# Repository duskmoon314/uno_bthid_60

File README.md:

# uno_bthid_60

Trying to diy a uno based, bluetooth HID 60 keyboard

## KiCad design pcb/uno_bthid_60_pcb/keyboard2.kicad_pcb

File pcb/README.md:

# README: uno_bthid_60_pcb

KiCAD project

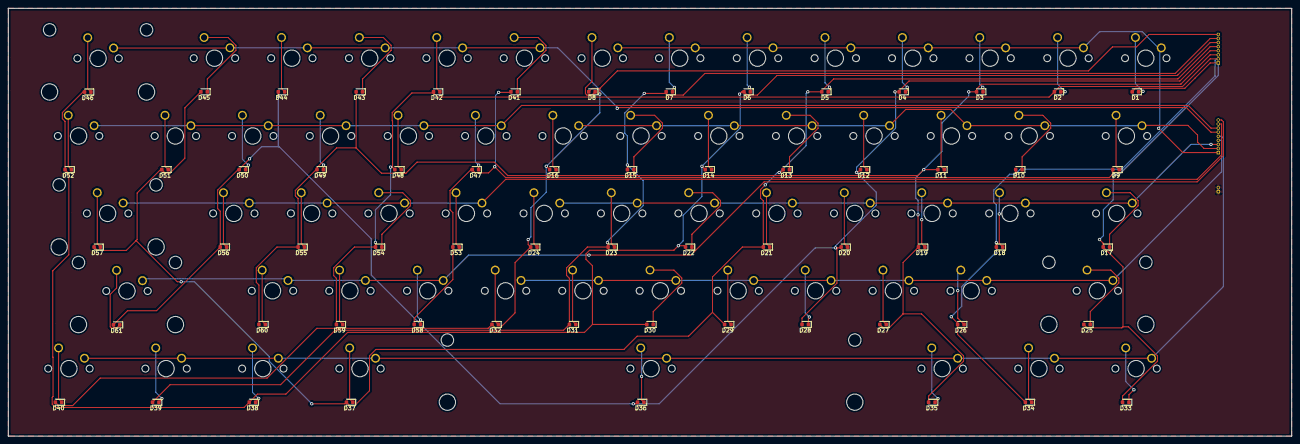
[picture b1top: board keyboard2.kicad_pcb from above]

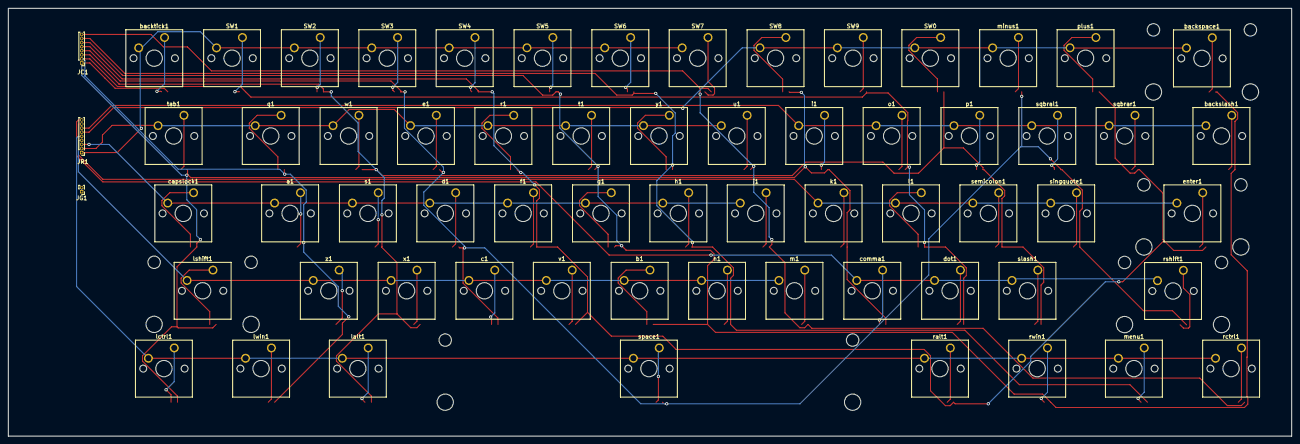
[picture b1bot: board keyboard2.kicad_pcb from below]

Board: 2 copper layers, 315.0 x 105.0 mm, 125 parts (64 on the bottom side), 79 nets.

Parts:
D1, D2, D3, D4, D5, D6, D7, D8, D9, D10, D11, D12, D13, D14, D15, D16, D17, D18, D19, D20, D21, D22, D23, D24, D25, D26, D27, D28, D29, D30, D31, D32, D33, D34, D35, D36, D37, D38, D39, D40, D41, D42, D43, D44, D45, D46, D47, D48, D49, D50, D51, D52, D53, D54, D55, D56, D57, D58, D59, D60, D61: DIODE; D_0603_1608Metric
JC1: Conn_01x08; PinHeader_1x08_P1.00mm_Vertical
JG1: Conn_01x02; PinHeader_1x02_P1.00mm_Vertical
JR1: Conn_01x09; PinHeader_1x09_P1.00mm_Vertical
SW0, SW1, SW2, SW3, SW4, SW5, SW6, SW7, SW8, SW9: SW_Push; SW_Cherry_MX_1.00u_PCB
a1: SW_Push; SW_Cherry_MX_1.00u_PCB
b1: SW_Push; SW_Cherry_MX_1.00u_PCB
backslash1: SW_Push; SW_Cherry_MX_1.50u_PCB
backspace1: SW_Push; SW_Cherry_MX_2.00u_PCB
backtick1: SW_Push; SW_Cherry_MX_1.00u_PCB
c1: SW_Push; SW_Cherry_MX_1.00u_PCB
capslock1: SW_Push; SW_Cherry_MX_1.75u_PCB
comma1: SW_Push; SW_Cherry_MX_1.00u_PCB
d1: SW_Push; SW_Cherry_MX_1.00u_PCB
dot1: SW_Push; SW_Cherry_MX_1.00u_PCB
e1: SW_Push; SW_Cherry_MX_1.00u_PCB
enter1: SW_Push; SW_Cherry_MX_2.25u_PCB
f1: SW_Push; SW_Cherry_MX_1.00u_PCB
g1: SW_Push; SW_Cherry_MX_1.00u_PCB
h1: SW_Push; SW_Cherry_MX_1.00u_PCB
i1: SW_Push; SW_Cherry_MX_1.00u_PCB
j1: SW_Push; SW_Cherry_MX_1.00u_PCB
k1: SW_Push; SW_Cherry_MX_1.00u_PCB
l1: SW_Push; SW_Cherry_MX_1.00u_PCB
lalt1: SW_Push; SW_Cherry_MX_1.25u_PCB
lctrl1: SW_Push; SW_Cherry_MX_1.25u_PCB
lshift1: SW_Push; SW_Cherry_MX_2.25u_PCB
lwin1: SW_Push; SW_Cherry_MX_1.25u_PCB
m1: SW_Push; SW_Cherry_MX_1.00u_PCB
menu1: SW_Push; SW_Cherry_MX_1.25u_PCB
minus1: SW_Push; SW_Cherry_MX_1.00u_PCB
n1: SW_Push; SW_Cherry_MX_1.00u_PCB
o1: SW_Push; SW_Cherry_MX_1.00u_PCB
p1: SW_Push; SW_Cherry_MX_1.00u_PCB
plus1: SW_Push; SW_Cherry_MX_1.00u_PCB
q1: SW_Push; SW_Cherry_MX_1.00u_PCB
r1: SW_Push; SW_Cherry_MX_1.00u_PCB
ralt1: SW_Push; SW_Cherry_MX_1.25u_PCB
rctrl1: SW_Push; SW_Cherry_MX_1.25u_PCB
rshift1: SW_Push; SW_Cherry_MX_2.75u_PCB
rwin1: SW_Push; SW_Cherry_MX_1.25u_PCB
s1: SW_Push; SW_Cherry_MX_1.00u_PCB
semicolon1: SW_Push; SW_Cherry_MX_1.00u_PCB
singquote1: SW_Push; SW_Cherry_MX_1.00u_PCB
slash1: SW_Push; SW_Cherry_MX_1.00u_PCB
space1: SW_Push; SW_Cherry_MX_6.25u_PCB
sqbral1: SW_Push; SW_Cherry_MX_1.00u_PCB
sqbrar1: SW_Push; SW_Cherry_MX_1.00u_PCB
t1: SW_Push; SW_Cherry_MX_1.00u_PCB
tab1: SW_Push; SW_Cherry_MX_1.50u_PCB
u1: SW_Push; SW_Cherry_MX_1.00u_PCB
v1: SW_Push; SW_Cherry_MX_1.00u_PCB
w1: SW_Push; SW_Cherry_MX_1.00u_PCB
x1: SW_Push; SW_Cherry_MX_1.00u_PCB
y1: SW_Push; SW_Cherry_MX_1.00u_PCB
z1: SW_Push; SW_Cherry_MX_1.00u_PCB

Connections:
/C1: D1.2, D9.2, D17.2, D25.2, D33.2, D41.2, D47.2, D53.2, D58.2, JC1.1
/C2: D2.2, D10.2, D18.2, D26.2, D34.2, D42.2, D48.2, D54.2, D59.2, JC1.2
/C3: D3.2, D11.2, D19.2, D27.2, D35.2, D43.2, D49.2, D55.2, D60.2, JC1.3
/C4: D4.2, D12.2, D20.2, D28.2, D36.2, D44.2, D50.2, D56.2, D61.2, JC1.4
/C5: D5.2, D13.2, D21.2, D29.2, D37.2, D45.2, D51.2, D57.2, JC1.5
/C6: D6.2, D14.2, D22.2, D30.2, D38.2, D46.2, D52.2, JC1.6
/C7: D7.2, D15.2, D23.2, D31.2, D39.2, JC1.7
/C8: D8.2, D16.2, D24.2, D32.2, D40.2, JC1.8
/R1: JR1.1, SW1.2, SW2.2, SW3.2, SW4.2, SW5.2, SW6.2, SW7.2, backtick1.2
/R2: JR1.2, e1.2, q1.2, r1.2, t1.2, tab1.2, u1.2, w1.2, y1.2
/R3: JR1.3, a1.2, capslock1.2, d1.2, f1.2, g1.2, h1.2, j1.2, s1.2
/R4: JR1.4, b1.2, c1.2, lshift1.2, m1.2, n1.2, v1.2, x1.2, z1.2
/R5: JR1.5, lalt1.2, lctrl1.2, lwin1.2, menu1.2, ralt1.2, rctrl1.2, rwin1.2, space1.2
/R6: JR1.6, SW0.2, SW8.2, SW9.2, backspace1.2, minus1.2, plus1.2
/R7: JR1.7, backslash1.2, i1.2, o1.2, p1.2, sqbral1.2, sqbrar1.2
/R8: JR1.8, enter1.2, k1.2, l1.2, semicolon1.2, singquote1.2
/R9: JR1.9, comma1.2, dot1.2, rshift1.2, slash1.2
GND: JG1.1, JG1.2
unnamed: D1.1, backtick1.1
unnamed: D2.1, SW1.1
unnamed: D3.1, SW2.1
unnamed: D4.1, SW3.1
unnamed: D5.1, SW4.1
unnamed: D6.1, SW5.1
unnamed: D7.1, SW6.1
unnamed: D8.1, SW7.1
unnamed: D9.1, tab1.1
unnamed: D10.1, q1.1
unnamed: D11.1, w1.1
unnamed: D12.1, e1.1
unnamed: D13.1, r1.1
unnamed: D14.1, t1.1
unnamed: D15.1, y1.1
unnamed: D16.1, u1.1
unnamed: D17.1, capslock1.1
unnamed: D18.1, a1.1
unnamed: D19.1, s1.1
unnamed: D20.1, d1.1
unnamed: D21.1, f1.1
unnamed: D22.1, g1.1
unnamed: D23.1, h1.1
unnamed: D24.1, j1.1
unnamed: D25.1, lshift1.1
unnamed: D26.1, z1.1
unnamed: D27.1, x1.1
unnamed: D28.1, c1.1
unnamed: D29.1, v1.1
unnamed: D30.1, b1.1
unnamed: D31.1, n1.1
unnamed: D32.1, m1.1
unnamed: D33.1, lctrl1.1
unnamed: D34.1, lwin1.1
unnamed: D35.1, lalt1.1
unnamed: D36.1, space1.1
unnamed: D37.1, ralt1.1
unnamed: D38.1, rwin1.1
unnamed: D39.1, menu1.1
unnamed: D40.1, rctrl1.1
unnamed: D41.1, SW8.1
unnamed: D42.1, SW9.1
unnamed: D43.1, SW0.1
unnamed: D44.1, minus1.1
unnamed: D45.1, plus1.1
unnamed: D46.1, backspace1.1
unnamed: D47.1, i1.1
unnamed: D48.1, o1.1
unnamed: D49.1, p1.1
unnamed: D50.1, sqbral1.1
unnamed: D51.1, sqbrar1.1
unnamed: D52.1, backslash1.1
unnamed: D53.1, k1.1
unnamed: D54.1, l1.1
unnamed: D55.1, semicolon1.1
unnamed: D56.1, singquote1.1
unnamed: D57.1, enter1.1
unnamed: D58.1, comma1.1
unnamed: D59.1, dot1.1
unnamed: D60.1, slash1.1
unnamed: D61.1, rshift1.1

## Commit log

2020-08-05 :tada: Initialize pio & kicad project
2020-08-14 add pcb design
    pcb with iopin pinheaders
2020-08-15 Add manual-wiring version
    auto: ugly ugly ugly
2020-08-15 driver 1.0
2020-08-16 Add PCB doc assets
2020-08-16 Add images
2020-08-16 Add pcb docs
2020-12-31 [ImgBot] Optimize images
    *Total -- 3,647.84kb -> 3,368.43kb (7.66%)
    /pcb/docs/assets/pcb2_sch.png -- 72.21kb -> 40.43kb (44%)
    /pcb/docs/assets/keyboard_matrix.png -- 230.67kb -> 160.88kb (30.25%)
    /docs/keyboard.png -- 63.89kb -> 45.03kb (29.51%)
    /pcb/docs/assets/pcb2_manual_3d.png -- 1,544.87kb -> 1,457.37kb (5.66%)
    /pcb/uno_bthid_60_pcb/keyboard2.png -- 1,736.21kb -> 1,664.72kb (4.12%)
2021-07-08 Add .whitesource configuration file
